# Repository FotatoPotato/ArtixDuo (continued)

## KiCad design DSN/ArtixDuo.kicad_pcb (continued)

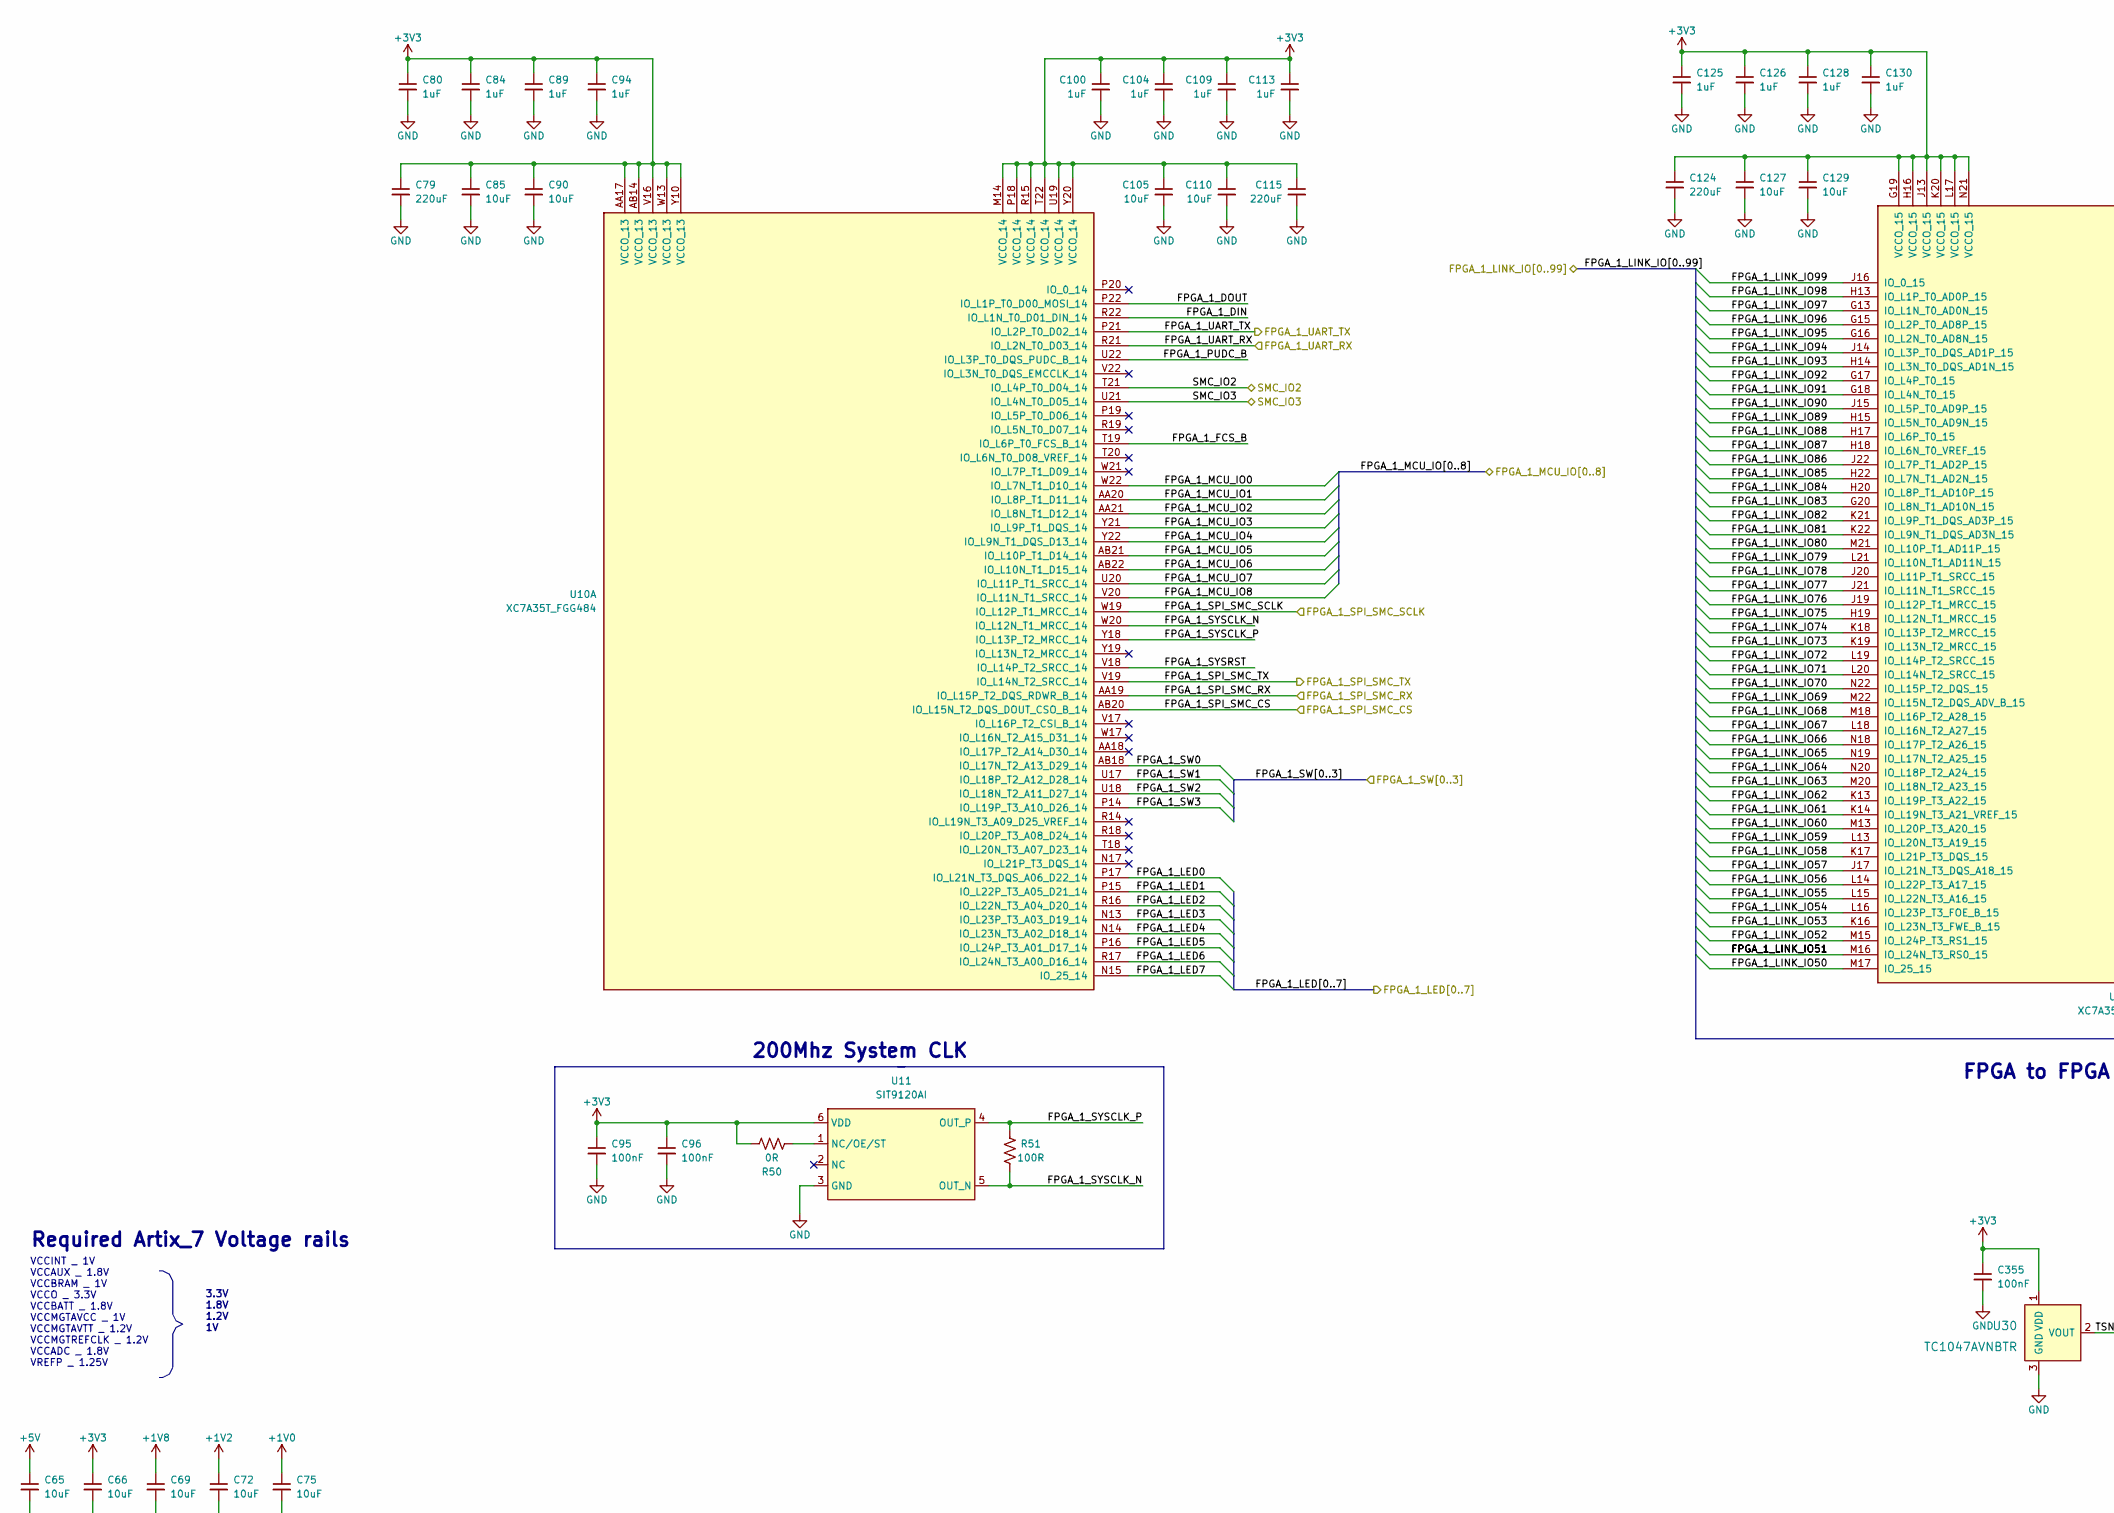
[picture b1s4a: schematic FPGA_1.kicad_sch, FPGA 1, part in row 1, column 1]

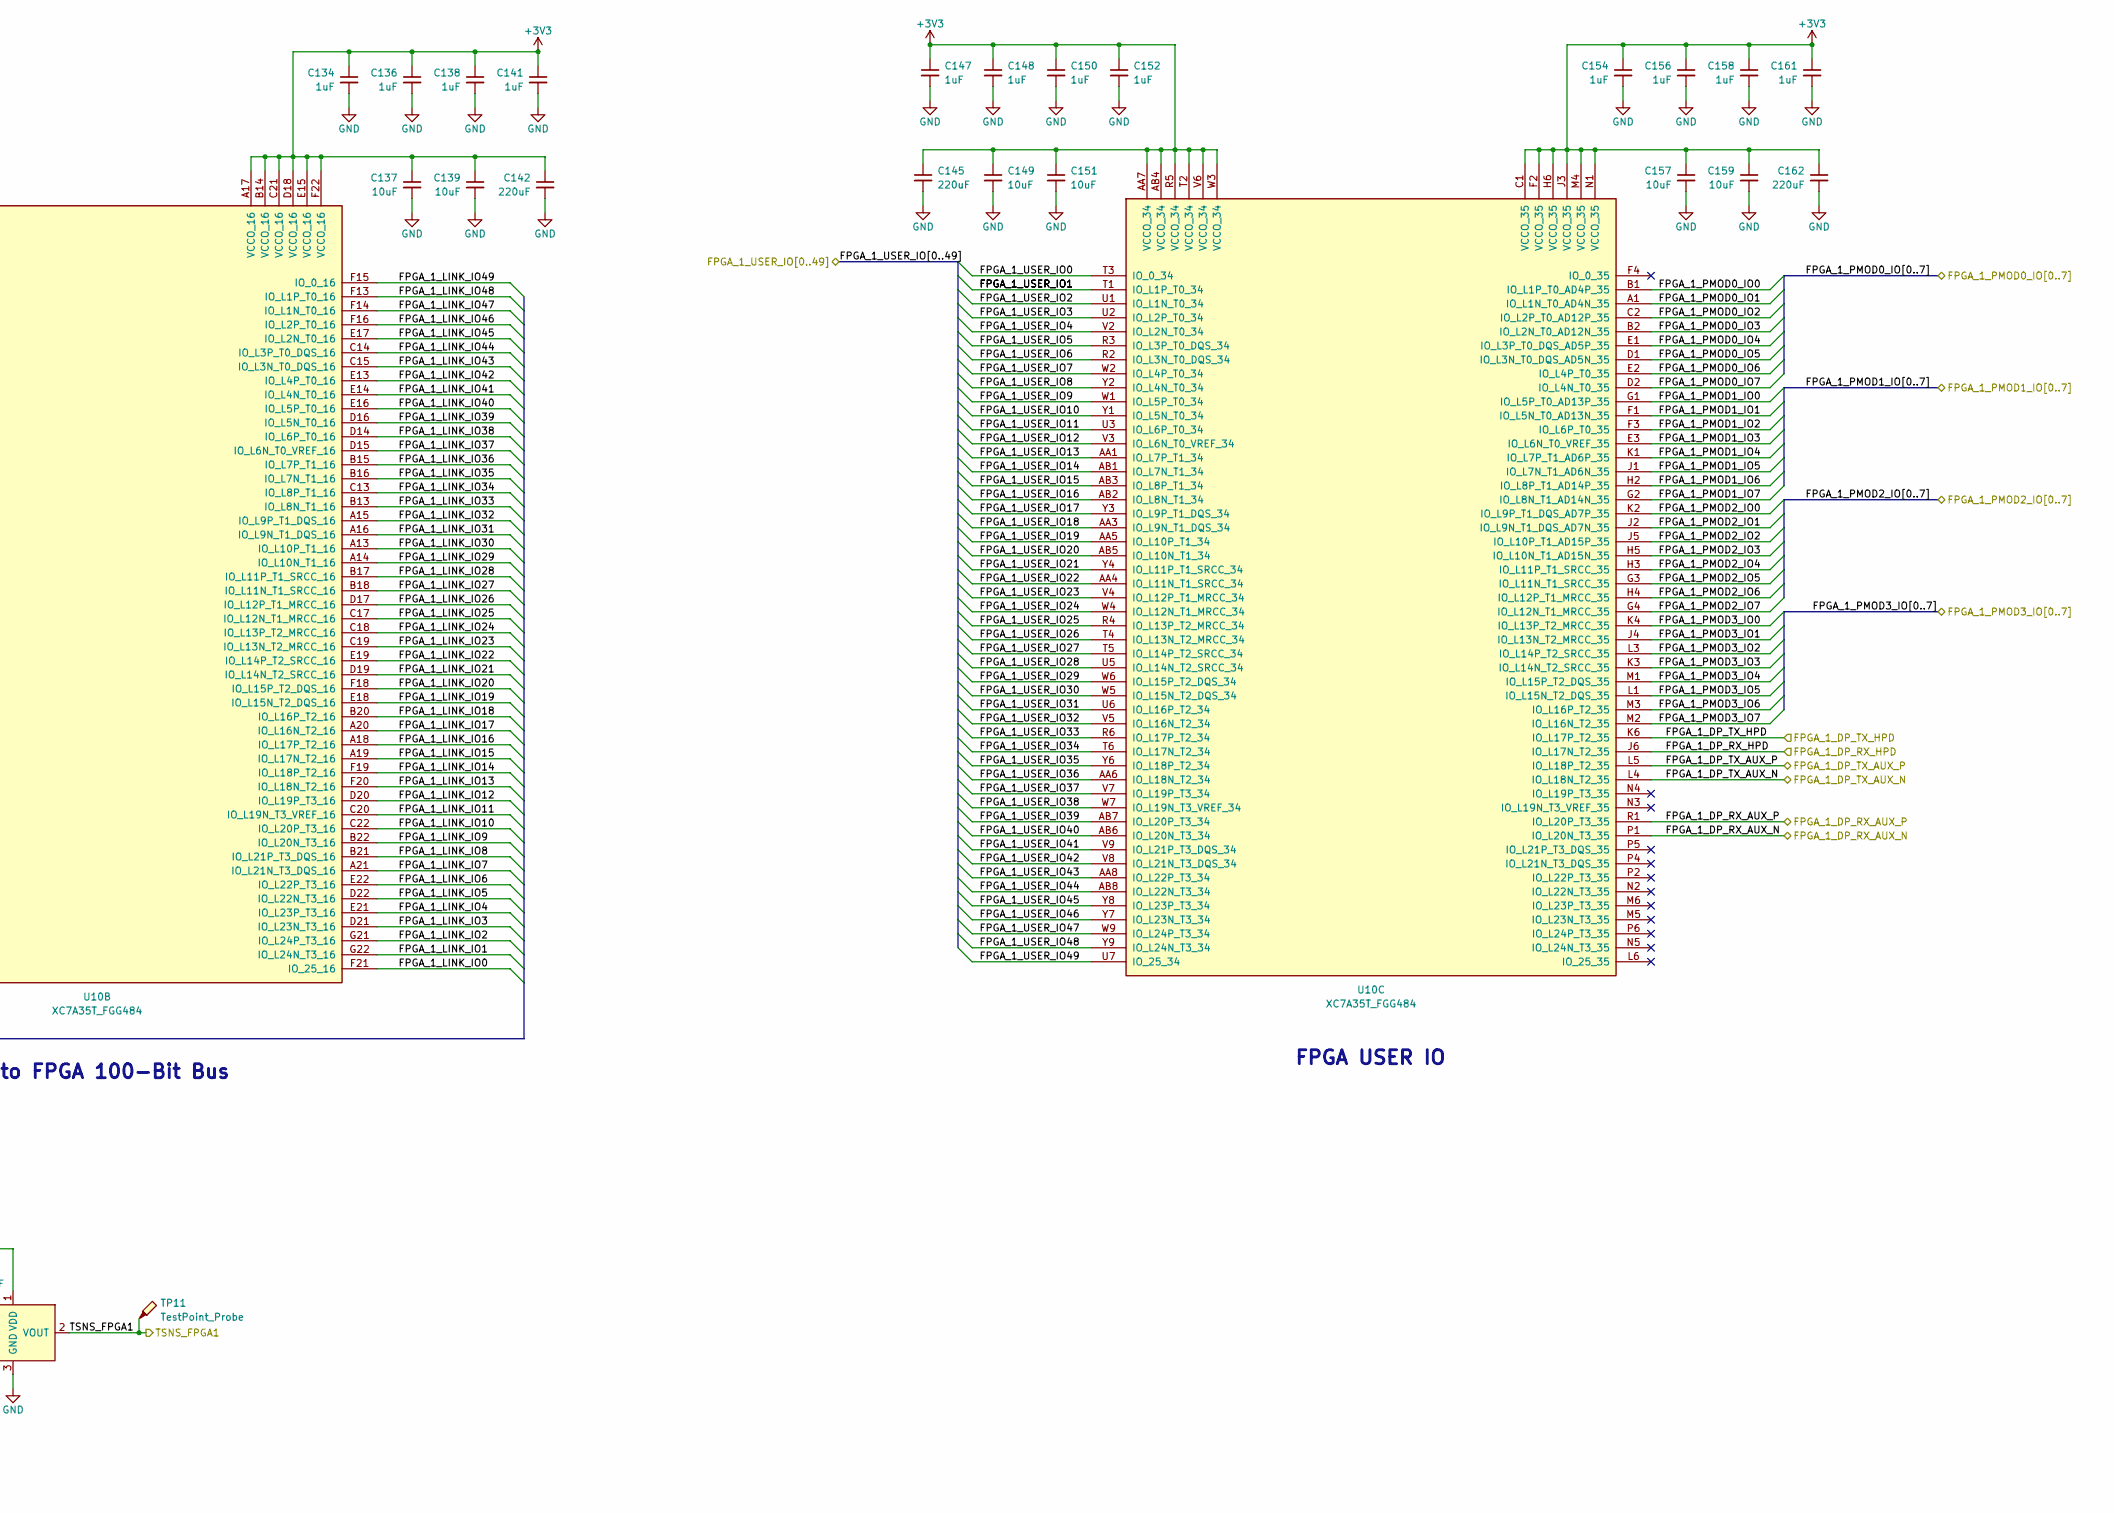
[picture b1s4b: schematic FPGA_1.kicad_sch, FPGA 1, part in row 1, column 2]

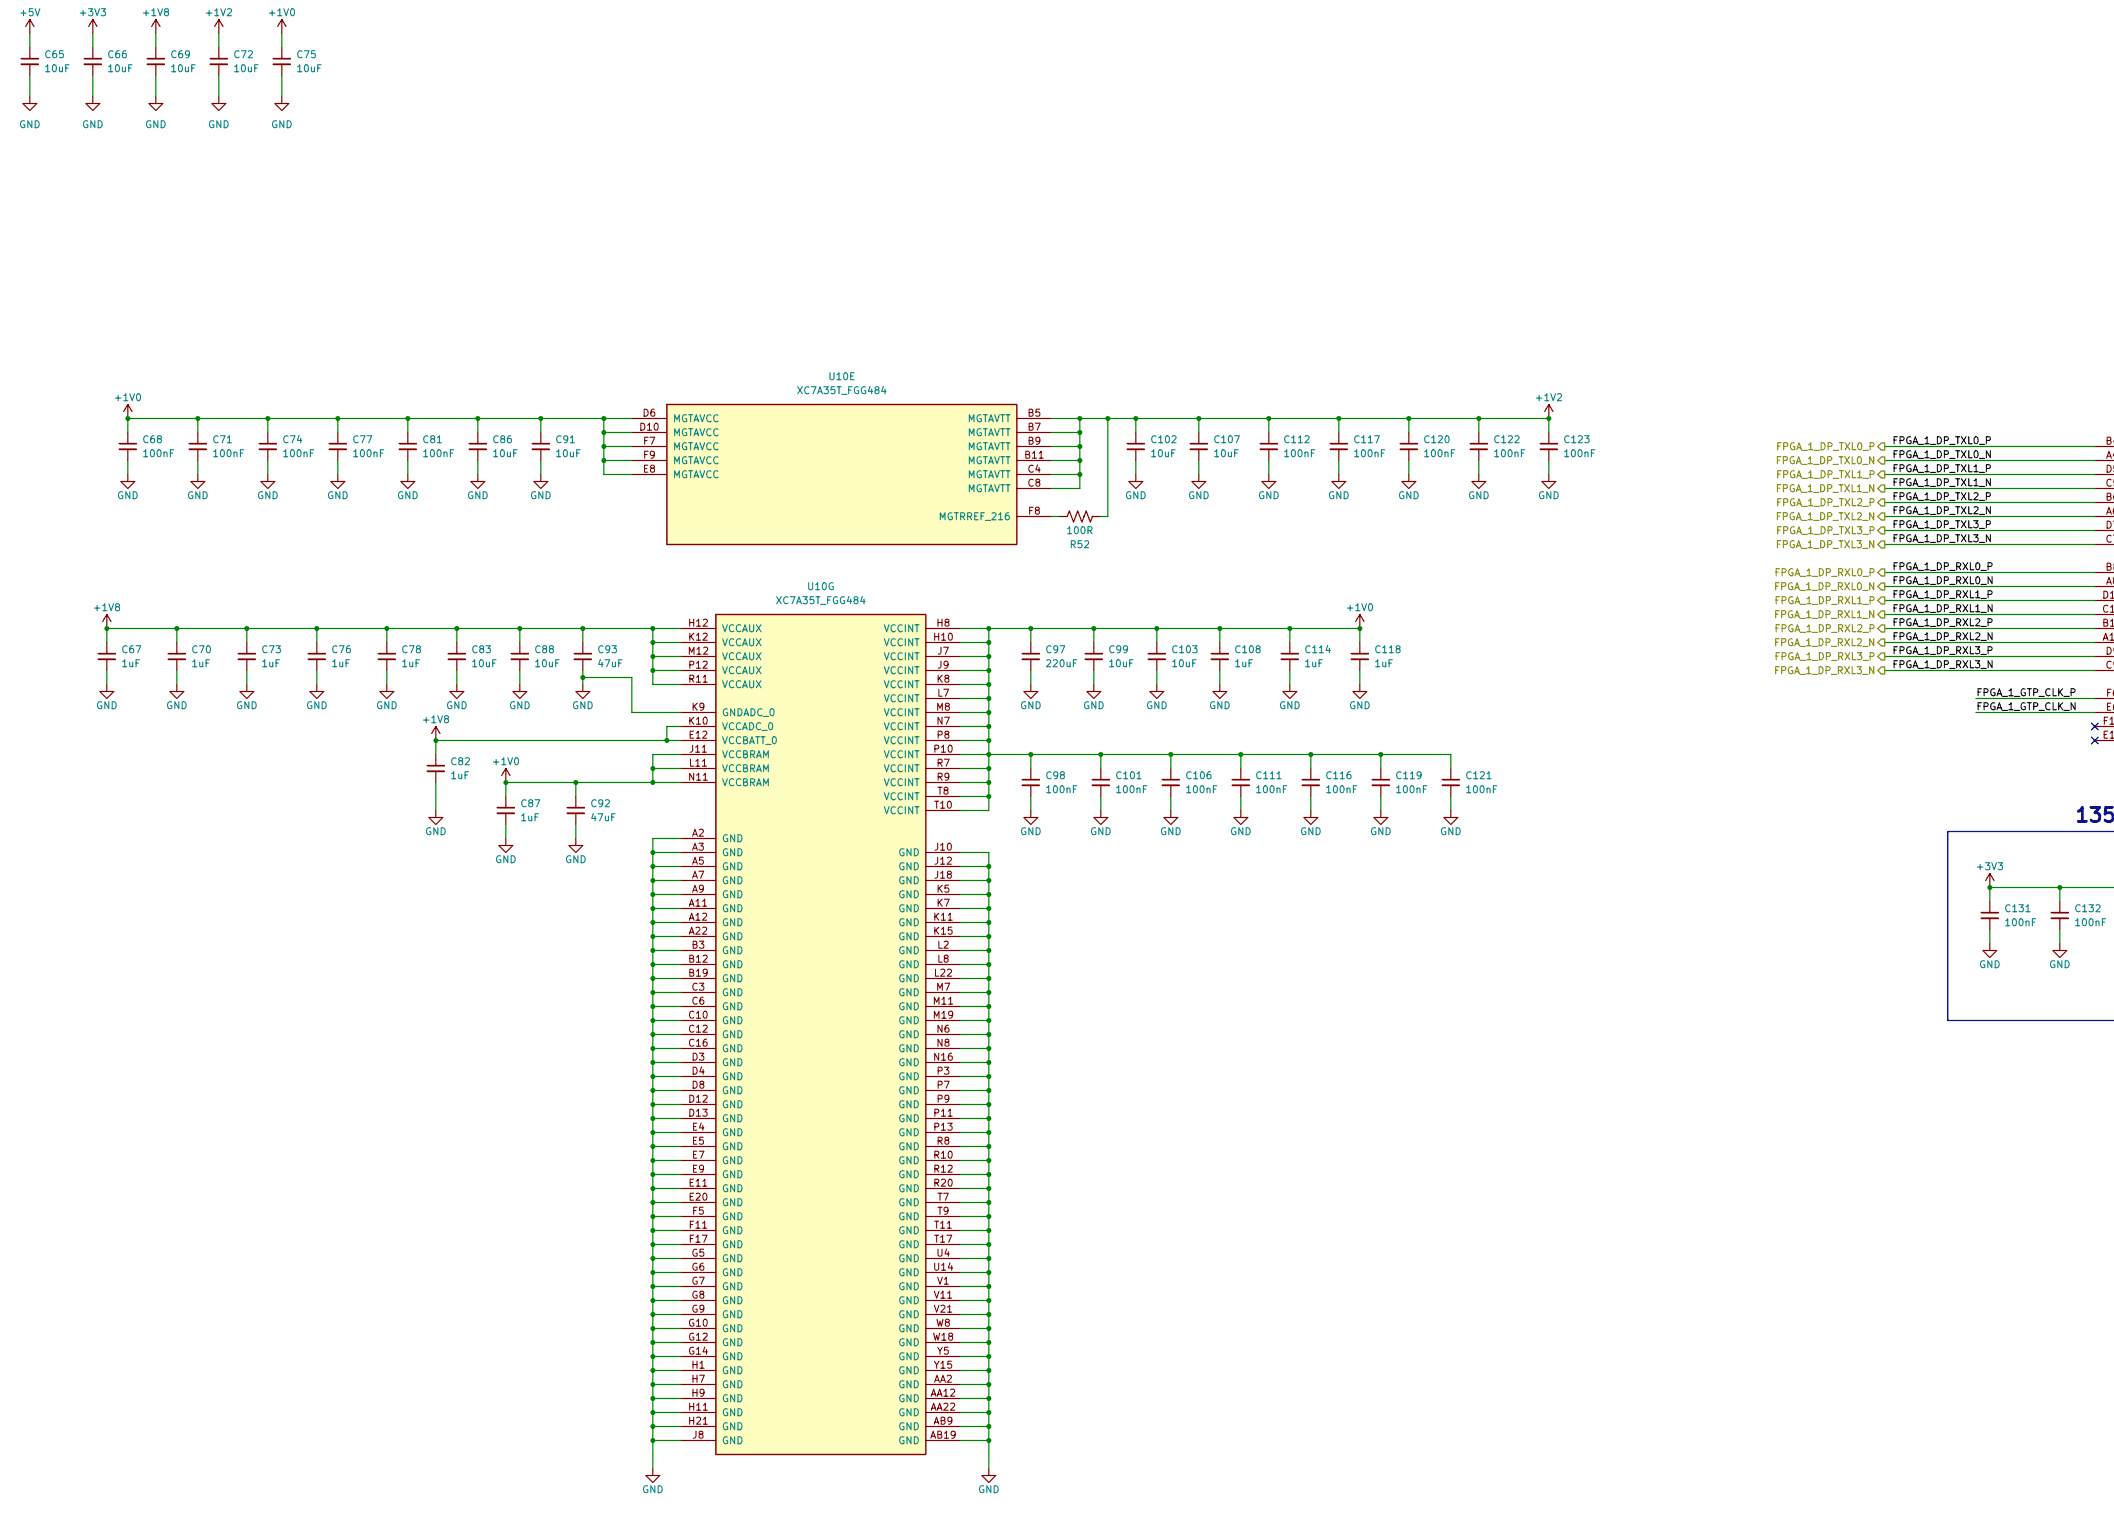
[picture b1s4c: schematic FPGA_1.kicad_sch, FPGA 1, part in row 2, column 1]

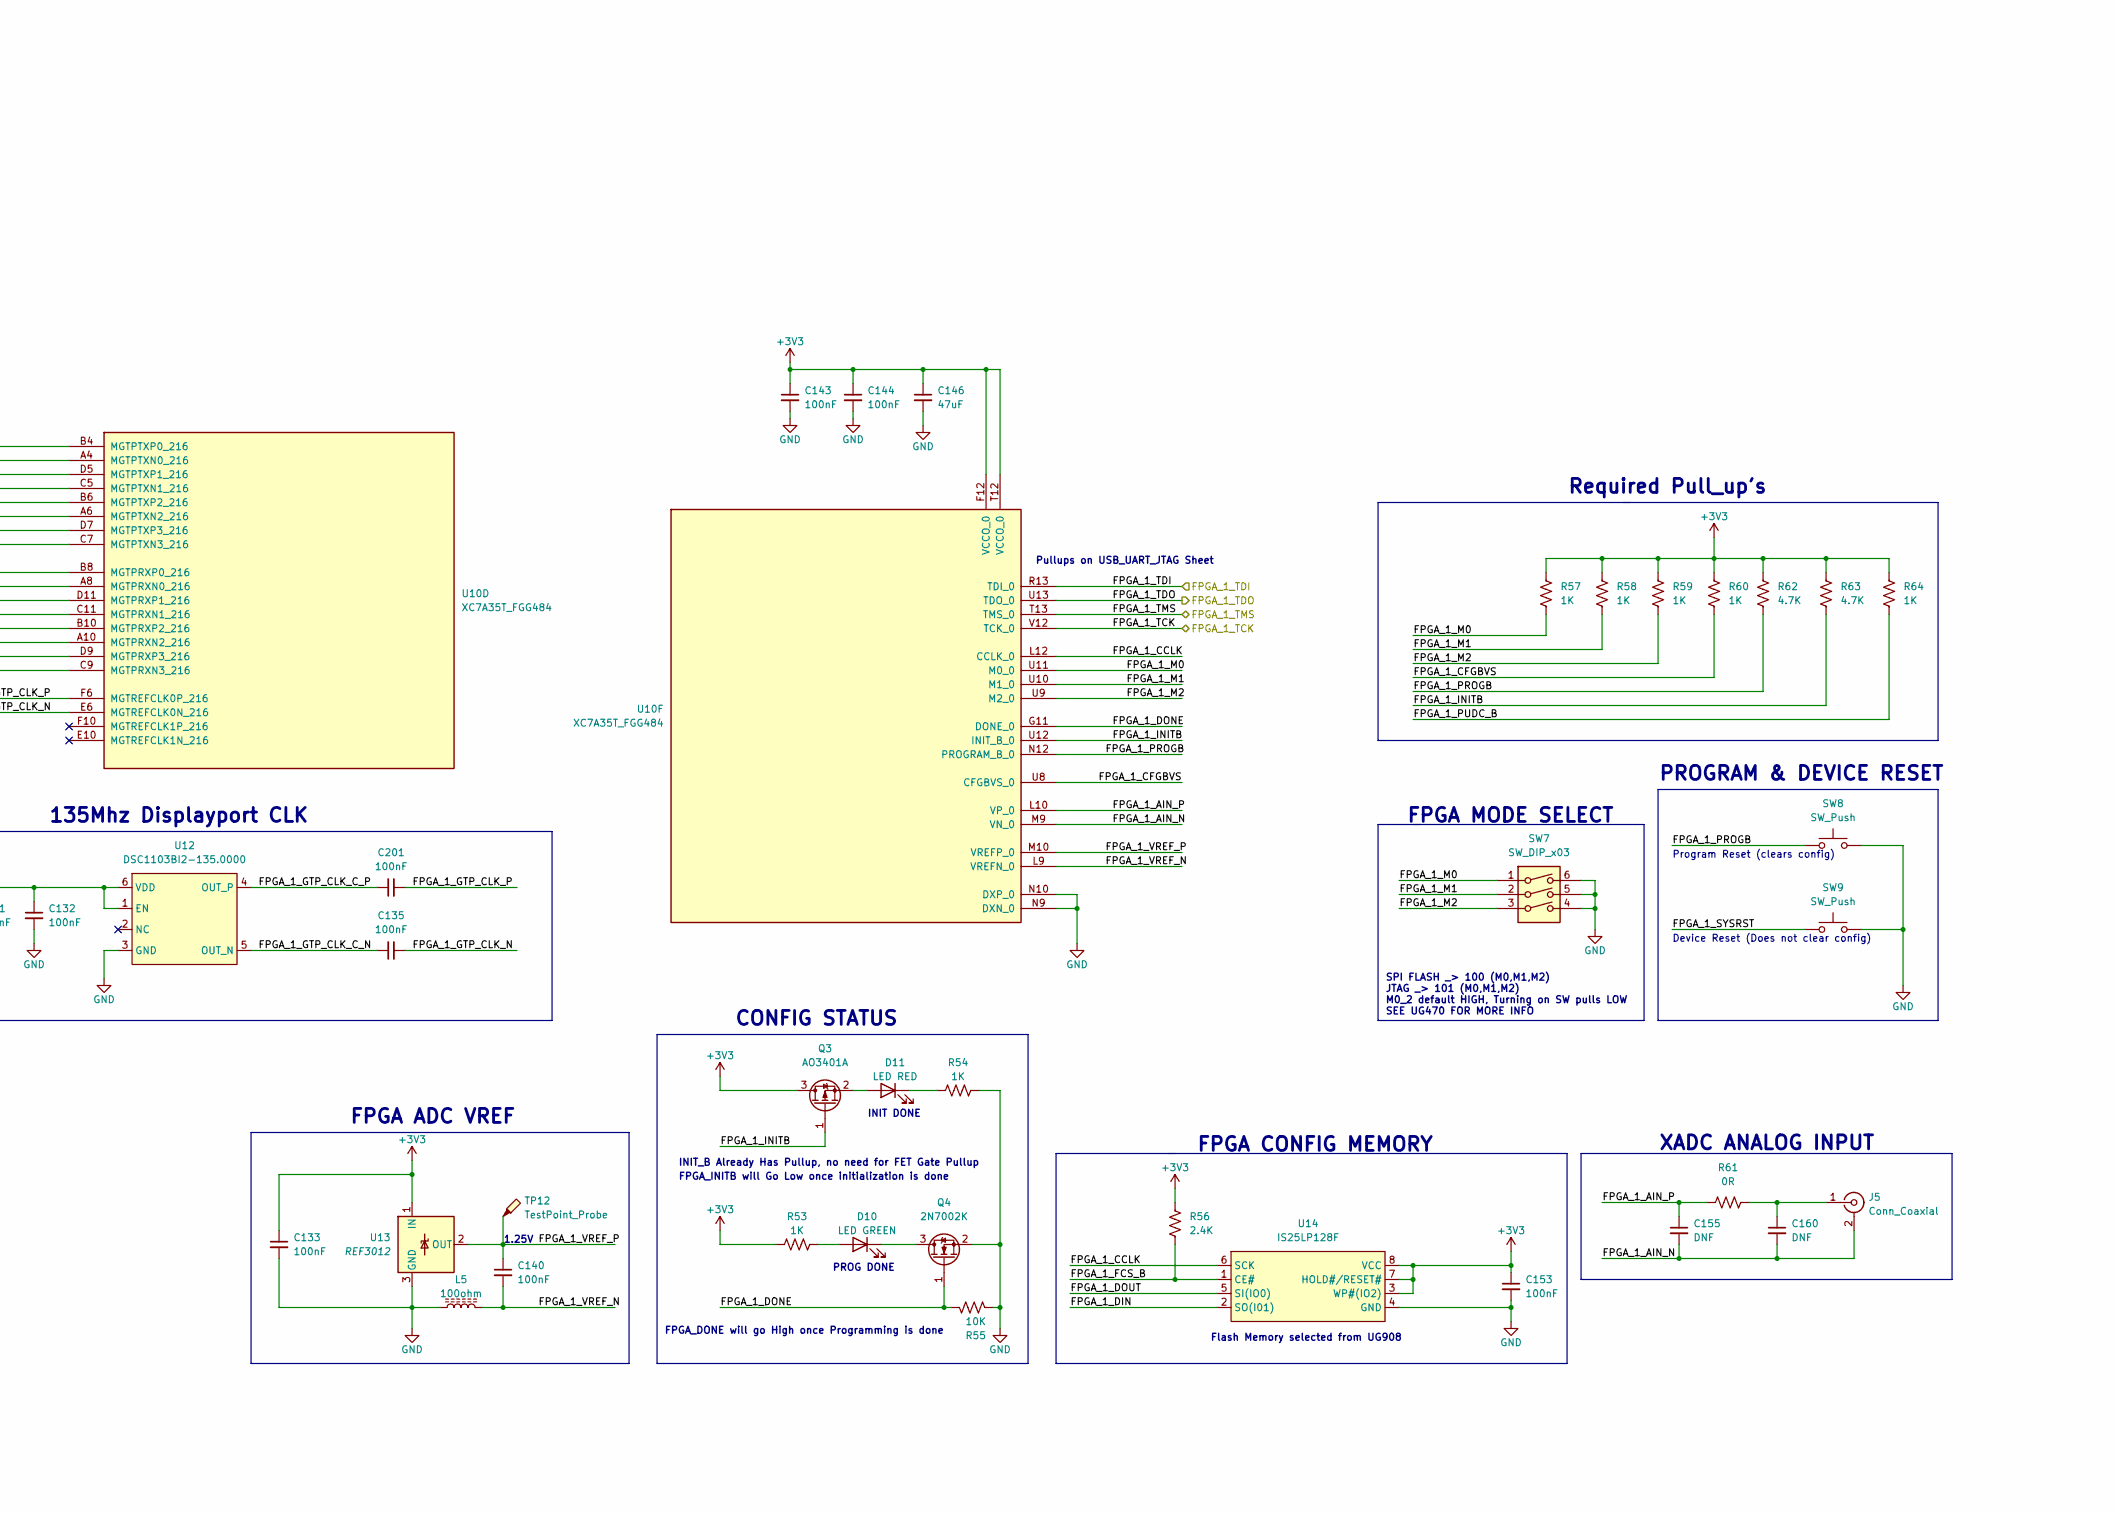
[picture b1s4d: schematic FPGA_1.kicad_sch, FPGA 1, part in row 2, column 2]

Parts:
C65, C66, C69, C72, C75: 10uF; C_0805_2012Metric; MFR PN GRM21BC71E106KE01K
C67, C70, C73, C76, C78, C80, C82, C84, C87, C89, C94, C100, C104, C108, C109, C113, C114, C118, C125, C126, C128, C130, C134, C136, C138, C141, C147, C148, C150, C152, C154, C156, C158, C161: 1uF; C_0402_1005Metric; MFR PN GRM153R61A105ME95D
C68, C71, C74, C77, C81, C95, C96, C98, C101, C106, C111, C112, C116, C117, C119, C120, C121, C122, C123, C131, C132, C135, C201: 100nF; C_0402_1005Metric; MFR PN GRM155R71E104KE14J
C79, C97, C115, C124, C142, C145, C162: 220uF; C_1210_3225Metric; MFR PN GRM32ER60J227ME05K
C83, C85, C86, C88, C90, C91, C99, C102, C103, C105, C107, C110, C127, C129, C137, C139, C149, C151, C157, C159: 10uF; C_0603_1608Metric; MFR PN GRM185R60J106ME15J
C92, C93: 47uF; C_1210_3225Metric; MFR PN GRM32ER70J476ME20L
C133, C140, C143, C144, C153, C355: 100nF; C_0402_1005Metric; MFR PN GRM155R71H104ME14J
C146: 47uF; C_1210_3225Metric
C155, C160: DNF; C_0402_1005Metric
D10: LED GREEN; LED_0603_1608Metric; MFR PN 150060VS75000
D11: LED RED; LED_0603_1608Metric; MFR PN 150060RS75000
J5: Conn_Coaxial; SMA_Amphenol_901-144_Vertical
L5: 100ohm; L_0402_1005Metric; MFR_PN 742792731
Q3: AO3401A; SOT-23
Q4: 2N7002K; SOT-23
R50, R61: 0R; R_0402_1005Metric
R51, R52: 100R; R_0402_1005Metric; MFR PN RC0402FR-07100RL
R53, R54, R57, R58, R59, R60, R64: 1K; R_0402_1005Metric
R55: 10K; R_0402_1005Metric; MFR PN RC0402FR-0710KP
R56: 2.4K; R_0402_1005Metric
R62, R63: 4.7K; R_0402_1005Metric
SW7: SW_DIP_x03; SW_DIP_SPSTx03_Slide_9.78x9.8mm_W8.61mm_P2.54mm
SW8, SW9: SW_Push; SW_Push_1P1T_NO_CK_KMR2
TP11, TP12: TestPoint_Probe; TestPoint_Loop_D2.50mm_Drill1.85mm
U10: XC7A35T_FGG484
U11: SIT9120AI; Oscillator_SMD_SiTime_SiT9121-6Pin_3.2x2.5mm
U12: DSC1103BI2-135.0000; VDFN-6
U13: REF3012; SOT-23
U14: IS25LP128F; SOIC-8_3.9x4.9mm_P1.27mm; MFR PN IS25LP128F-JBLA3
U30: TC1047AVNBTR; SOT-23-3; MPN TC1047AVNBTR; Digi-Key_PN TC1047AVNBCT-ND

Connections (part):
+1V0: C68.1, C71.1, C74.1, C75.1, C77.1, C81.1, C86.1, C87.1, C91.1, C92.1, C97.1, C98.1, C99.1, C101.1, C103.1, C106.1, C108.1, C111.1, C114.1, C116.1, C118.1, C119.1, C121.1, U10.D6 (MGTAVCC), U10.D10 (MGTAVCC), U10.E8 (MGTAVCC), U10.F7 (MGTAVCC), U10.F9 (MGTAVCC), U10.H8 (VCCINT), U10.H10 (VCCINT), U10.J7 (VCCINT), U10.J9 (VCCINT), U10.J11 (VCCBRAM), U10.K8 (VCCINT), U10.L7 (VCCINT), U10.L11 (VCCBRAM), U10.M8 (VCCINT), U10.N7 (VCCINT), U10.N11 (VCCBRAM), U10.P8 (VCCINT), U10.P10 (VCCINT), U10.R7 (VCCINT), U10.R9 (VCCINT), U10.T8 (VCCINT), U10.T10 (VCCINT); also elsewhere on the board
+1V2: C72.1, C102.1, C107.1, C112.1, C117.1, C120.1, C122.1, C123.1, R52.2, U10.B5 (MGTAVTT), U10.B7 (MGTAVTT), U10.B9 (MGTAVTT), U10.B11 (MGTAVTT), U10.C4 (MGTAVTT), U10.C8 (MGTAVTT); also elsewhere on the board
+1V8: C67.1, C69.1, C70.1, C73.1, C76.1, C78.1, C82.1, C83.1, C88.1, C93.1, U10.E12 (VCCBATT_0), U10.H12 (VCCAUX), U10.K10 (VCCADC_0), U10.K12 (VCCAUX), U10.M12 (VCCAUX), U10.P12 (VCCAUX), U10.R11 (VCCAUX); also elsewhere on the board
+3V3: C66.1, C79.1, C80.1, C84.1, C85.1, C89.1, C90.1, C94.1, C95.1, C96.1, C100.1, C104.1, C105.1, C109.1, C110.1, C113.1, C115.1, C124.1, C125.1, C126.1, C127.1, C128.1, C129.1, C130.1, C131.1, C132.1, C133.1, C134.1, C136.1, C137.1, C138.1, C139.1, C141.1, C142.1, C143.1, C144.1, C145.1, C146.1, C147.1, C148.1, C149.1, C150.1, C151.1, C152.1, C153.1, C154.1, C156.1, C157.1, C158.1, C159.1, C161.1, C162.1, C355.1, Q3.3 (D), R50.1, R53.2, R56.2, R57.2, R58.2, R59.2, R60.2, R62.2, R63.2, R64.2, U10.A17 (VCCO_16), U10.AA7 (VCCO_34), U10.AA17 (VCCO_13), U10.AB4 (VCCO_34), U10.AB14 (VCCO_13), U10.B14 (VCCO_16), U10.C1 (VCCO_35), U10.C21 (VCCO_16), U10.D18 (VCCO_16), U10.E15 (VCCO_16), U10.F2 (VCCO_35), U10.F12 (VCCO_0), U10.F22 (VCCO_16), U10.G19 (VCCO_15), U10.H6 (VCCO_35), U10.H16 (VCCO_15), U10.J3 (VCCO_35), U10.J13 (VCCO_15)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; also elsewhere on the board
/TopSheet/FPGA_0/FPGA_0_LINK_IO0: U10.F21 (IO_25_16); also elsewhere on the board
/TopSheet/FPGA_0/FPGA_0_LINK_IO1: U10.G22 (IO_L24N_T3_16); also elsewhere on the board
/TopSheet/FPGA_0/FPGA_0_LINK_IO2: U10.G21 (IO_L24P_T3_16); also elsewhere on the board
/TopSheet/FPGA_0/FPGA_0_LINK_IO3: U10.D21 (IO_L23N_T3_16); also elsewhere on the board
/TopSheet/FPGA_0/FPGA_0_LINK_IO4: U10.E21 (IO_L23P_T3_16); also elsewhere on the board
/TopSheet/FPGA_0/FPGA_0_LINK_IO5: U10.D22 (IO_L22N_T3_16); also elsewhere on the board
/TopSheet/FPGA_0/FPGA_0_LINK_IO6: U10.E22 (IO_L22P_T3_16); also elsewhere on the board
/TopSheet/FPGA_0/FPGA_0_LINK_IO7: U10.A21 (IO_L21N_T3_DQS_16); also elsewhere on the board
/TopSheet/FPGA_0/FPGA_0_LINK_IO8: U10.B21 (IO_L21P_T3_DQS_16); also elsewhere on the board
/TopSheet/FPGA_0/FPGA_0_LINK_IO9: U10.B22 (IO_L20N_T3_16); also elsewhere on the board
/TopSheet/FPGA_0/FPGA_0_LINK_IO10: U10.C22 (IO_L20P_T3_16); also elsewhere on the board
/TopSheet/FPGA_0/FPGA_0_LINK_IO11: U10.C20 (IO_L19N_T3_VREF_16); also elsewhere on the board
/TopSheet/FPGA_0/FPGA_0_LINK_IO12: U10.D20 (IO_L19P_T3_16); also elsewhere on the board
/TopSheet/FPGA_0/FPGA_0_LINK_IO13: U10.F20 (IO_L18N_T2_16); also elsewhere on the board
/TopSheet/FPGA_0/FPGA_0_LINK_IO14: U10.F19 (IO_L18P_T2_16); also elsewhere on the board
/TopSheet/FPGA_0/FPGA_0_LINK_IO15: U10.A19 (IO_L17N_T2_16); also elsewhere on the board
/TopSheet/FPGA_0/FPGA_0_LINK_IO16: U10.A18 (IO_L17P_T2_16); also elsewhere on the board
/TopSheet/FPGA_0/FPGA_0_LINK_IO17: U10.A20 (IO_L16N_T2_16); also elsewhere on the board
/TopSheet/FPGA_0/FPGA_0_LINK_IO18: U10.B20 (IO_L16P_T2_16); also elsewhere on the board
/TopSheet/FPGA_0/FPGA_0_LINK_IO19: U10.E18 (IO_L15N_T2_DQS_16); also elsewhere on the board
/TopSheet/FPGA_0/FPGA_0_LINK_IO20: U10.F18 (IO_L15P_T2_DQS_16); also elsewhere on the board
/TopSheet/FPGA_0/FPGA_0_LINK_IO21: U10.D19 (IO_L14N_T2_SRCC_16); also elsewhere on the board
/TopSheet/FPGA_0/FPGA_0_LINK_IO22: U10.E19 (IO_L14P_T2_SRCC_16); also elsewhere on the board
/TopSheet/FPGA_0/FPGA_0_LINK_IO23: U10.C19 (IO_L13N_T2_MRCC_16); also elsewhere on the board
/TopSheet/FPGA_0/FPGA_0_LINK_IO24: U10.C18 (IO_L13P_T2_MRCC_16); also elsewhere on the board
/TopSheet/FPGA_0/FPGA_0_LINK_IO25: U10.C17 (IO_L12N_T1_MRCC_16); also elsewhere on the board
/TopSheet/FPGA_0/FPGA_0_LINK_IO26: U10.D17 (IO_L12P_T1_MRCC_16); also elsewhere on the board
/TopSheet/FPGA_0/FPGA_0_LINK_IO27: U10.B18 (IO_L11N_T1_SRCC_16); also elsewhere on the board
/TopSheet/FPGA_0/FPGA_0_LINK_IO28: U10.B17 (IO_L11P_T1_SRCC_16); also elsewhere on the board
/TopSheet/FPGA_0/FPGA_0_LINK_IO29: U10.A14 (IO_L10N_T1_16); also elsewhere on the board
/TopSheet/FPGA_0/FPGA_0_LINK_IO30: U10.A13 (IO_L10P_T1_16); also elsewhere on the board
/TopSheet/FPGA_0/FPGA_0_LINK_IO31: U10.A16 (IO_L9N_T1_DQS_16); also elsewhere on the board
/TopSheet/FPGA_0/FPGA_0_LINK_IO32: U10.A15 (IO_L9P_T1_DQS_16); also elsewhere on the board
/TopSheet/FPGA_0/FPGA_0_LINK_IO33: U10.B13 (IO_L8N_T1_16); also elsewhere on the board
/TopSheet/FPGA_0/FPGA_0_LINK_IO34: U10.C13 (IO_L8P_T1_16); also elsewhere on the board
/TopSheet/FPGA_0/FPGA_0_LINK_IO35: U10.B16 (IO_L7N_T1_16); also elsewhere on the board
/TopSheet/FPGA_0/FPGA_0_LINK_IO36: U10.B15 (IO_L7P_T1_16); also elsewhere on the board
/TopSheet/FPGA_0/FPGA_0_LINK_IO37: U10.D15 (IO_L6N_T0_VREF_16); also elsewhere on the board
/TopSheet/FPGA_0/FPGA_0_LINK_IO38: U10.D14 (IO_L6P_T0_16); also elsewhere on the board
/TopSheet/FPGA_0/FPGA_0_LINK_IO39: U10.D16 (IO_L5N_T0_16); also elsewhere on the board
/TopSheet/FPGA_0/FPGA_0_LINK_IO40: U10.E16 (IO_L5P_T0_16); also elsewhere on the board
/TopSheet/FPGA_0/FPGA_0_LINK_IO41: U10.E14 (IO_L4N_T0_16); also elsewhere on the board
/TopSheet/FPGA_0/FPGA_0_LINK_IO42: U10.E13 (IO_L4P_T0_16); also elsewhere on the board
/TopSheet/FPGA_0/FPGA_0_LINK_IO43: U10.C15 (IO_L3N_T0_DQS_16); also elsewhere on the board
/TopSheet/FPGA_0/FPGA_0_LINK_IO44: U10.C14 (IO_L3P_T0_DQS_16); also elsewhere on the board
/TopSheet/FPGA_0/FPGA_0_LINK_IO45: U10.E17 (IO_L2N_T0_16); also elsewhere on the board
/TopSheet/FPGA_0/FPGA_0_LINK_IO46: U10.F16 (IO_L2P_T0_16); also elsewhere on the board
/TopSheet/FPGA_0/FPGA_0_LINK_IO47: U10.F14 (IO_L1N_T0_16); also elsewhere on the board
/TopSheet/FPGA_0/FPGA_0_LINK_IO48: U10.F13 (IO_L1P_T0_16); also elsewhere on the board
/TopSheet/FPGA_0/FPGA_0_LINK_IO49: U10.F15 (IO_0_16); also elsewhere on the board
/TopSheet/FPGA_0/FPGA_0_LINK_IO50: U10.M17 (IO_25_15); also elsewhere on the board
/TopSheet/FPGA_0/FPGA_0_LINK_IO52: U10.M15 (IO_L24P_T3_RS1_15); also elsewhere on the board
/TopSheet/FPGA_0/FPGA_0_LINK_IO53: U10.K16 (IO_L23N_T3_FWE_B_15); also elsewhere on the board
/TopSheet/FPGA_0/FPGA_0_LINK_IO54: U10.L16 (IO_L23P_T3_FOE_B_15); also elsewhere on the board
/TopSheet/FPGA_0/FPGA_0_LINK_IO55: U10.L15 (IO_L22N_T3_A16_15); also elsewhere on the board
/TopSheet/FPGA_0/FPGA_0_LINK_IO56: U10.L14 (IO_L22P_T3_A17_15); also elsewhere on the board
/TopSheet/FPGA_0/FPGA_0_LINK_IO57: U10.J17 (IO_L21N_T3_DQS_A18_15); also elsewhere on the board
/TopSheet/FPGA_0/FPGA_0_LINK_IO58: U10.K17 (IO_L21P_T3_DQS_15); also elsewhere on the board
/TopSheet/FPGA_0/FPGA_0_LINK_IO59: U10.L13 (IO_L20N_T3_A19_15); also elsewhere on the board
/TopSheet/FPGA_0/FPGA_0_LINK_IO60: U10.M13 (IO_L20P_T3_A20_15); also elsewhere on the board
/TopSheet/FPGA_0/FPGA_0_LINK_IO61: U10.K14 (IO_L19N_T3_A21_VREF_15); also elsewhere on the board
/TopSheet/FPGA_0/FPGA_0_LINK_IO62: U10.K13 (IO_L19P_T3_A22_15); also elsewhere on the board
/TopSheet/FPGA_0/FPGA_0_LINK_IO63: U10.M20 (IO_L18N_T2_A23_15); also elsewhere on the board
/TopSheet/FPGA_0/FPGA_0_LINK_IO64: U10.N20 (IO_L18P_T2_A24_15); also elsewhere on the board
/TopSheet/FPGA_0/FPGA_0_LINK_IO65: U10.N19 (IO_L17N_T2_A25_15); also elsewhere on the board
/TopSheet/FPGA_0/FPGA_0_LINK_IO66: U10.N18 (IO_L17P_T2_A26_15); also elsewhere on the board
/TopSheet/FPGA_0/FPGA_0_LINK_IO67: U10.L18 (IO_L16N_T2_A27_15); also elsewhere on the board
/TopSheet/FPGA_0/FPGA_0_LINK_IO68: U10.M18 (IO_L16P_T2_A28_15); also elsewhere on the board
/TopSheet/FPGA_0/FPGA_0_LINK_IO69: U10.M22 (IO_L15N_T2_DQS_ADV_B_15); also elsewhere on the board
/TopSheet/FPGA_0/FPGA_0_LINK_IO70: U10.N22 (IO_L15P_T2_DQS_15); also elsewhere on the board
/TopSheet/FPGA_0/FPGA_0_LINK_IO71: U10.L20 (IO_L14N_T2_SRCC_15); also elsewhere on the board
/TopSheet/FPGA_0/FPGA_0_LINK_IO72: U10.L19 (IO_L14P_T2_SRCC_15); also elsewhere on the board
/TopSheet/FPGA_0/FPGA_0_LINK_IO73: U10.K19 (IO_L13N_T2_MRCC_15); also elsewhere on the board
/TopSheet/FPGA_0/FPGA_0_LINK_IO74: U10.K18 (IO_L13P_T2_MRCC_15); also elsewhere on the board
/TopSheet/FPGA_0/FPGA_0_LINK_IO75: U10.H19 (IO_L12N_T1_MRCC_15); also elsewhere on the board
/TopSheet/FPGA_0/FPGA_0_LINK_IO76: U10.J19 (IO_L12P_T1_MRCC_15); also elsewhere on the board
/TopSheet/FPGA_0/FPGA_0_LINK_IO77: U10.J21 (IO_L11N_T1_SRCC_15); also elsewhere on the board
/TopSheet/FPGA_0/FPGA_0_LINK_IO78: U10.J20 (IO_L11P_T1_SRCC_15); also elsewhere on the board
/TopSheet/FPGA_0/FPGA_0_LINK_IO79: U10.L21 (IO_L10N_T1_AD11N_15); also elsewhere on the board
/TopSheet/FPGA_0/FPGA_0_LINK_IO80: U10.M21 (IO_L10P_T1_AD11P_15); also elsewhere on the board
/TopSheet/FPGA_0/FPGA_0_LINK_IO81: U10.K22 (IO_L9N_T1_DQS_AD3N_15); also elsewhere on the board
/TopSheet/FPGA_0/FPGA_0_LINK_IO82: U10.K21 (IO_L9P_T1_DQS_AD3P_15); also elsewhere on the board
/TopSheet/FPGA_0/FPGA_0_LINK_IO83: U10.G20 (IO_L8N_T1_AD10N_15); also elsewhere on the board
/TopSheet/FPGA_0/FPGA_0_LINK_IO84: U10.H20 (IO_L8P_T1_AD10P_15); also elsewhere on the board
/TopSheet/FPGA_0/FPGA_0_LINK_IO85: U10.H22 (IO_L7N_T1_AD2N_15); also elsewhere on the board
/TopSheet/FPGA_0/FPGA_0_LINK_IO86: U10.J22 (IO_L7P_T1_AD2P_15); also elsewhere on the board
/TopSheet/FPGA_0/FPGA_0_LINK_IO87: U10.H18 (IO_L6N_T0_VREF_15); also elsewhere on the board
/TopSheet/FPGA_0/FPGA_0_LINK_IO88: U10.H17 (IO_L6P_T0_15); also elsewhere on the board
/TopSheet/FPGA_0/FPGA_0_LINK_IO89: U10.H15 (IO_L5N_T0_AD9N_15); also elsewhere on the board
/TopSheet/FPGA_0/FPGA_0_LINK_IO90: U10.J15 (IO_L5P_T0_AD9P_15); also elsewhere on the board
/TopSheet/FPGA_0/FPGA_0_LINK_IO91: U10.G18 (IO_L4N_T0_15); also elsewhere on the board
/TopSheet/FPGA_0/FPGA_0_LINK_IO92: U10.G17 (IO_L4P_T0_15); also elsewhere on the board
/TopSheet/FPGA_0/FPGA_0_LINK_IO93: U10.H14 (IO_L3N_T0_DQS_AD1N_15); also elsewhere on the board
/TopSheet/FPGA_0/FPGA_0_LINK_IO94: U10.J14 (IO_L3P_T0_DQS_AD1P_15); also elsewhere on the board
/TopSheet/FPGA_0/FPGA_0_LINK_IO95: U10.G16 (IO_L2N_T0_AD8N_15); also elsewhere on the board
/TopSheet/FPGA_0/FPGA_0_LINK_IO96: U10.G15 (IO_L2P_T0_AD8P_15); also elsewhere on the board
/TopSheet/FPGA_0/FPGA_0_LINK_IO97: U10.G13 (IO_L1N_T0_AD0N_15); also elsewhere on the board
/TopSheet/FPGA_0/FPGA_0_LINK_IO98: U10.H13 (IO_L1P_T0_AD0P_15); also elsewhere on the board
/TopSheet/FPGA_0/FPGA_0_LINK_IO99: U10.J16 (IO_0_15); also elsewhere on the board
/TopSheet/FPGA_1/FPGA_1_AIN_N: C155.2, C160.2, J5.2 (Ext), U10.M9 (VN_0)
/TopSheet/FPGA_1/FPGA_1_AIN_P: C155.1, R61.1, U10.L10 (VP_0)
/TopSheet/FPGA_1/FPGA_1_CCLK: U10.L12 (CCLK_0), U14.6 (SCK)
/TopSheet/FPGA_1/FPGA_1_CFGBVS: R60.1, U10.U8 (CFGBVS_0)
/TopSheet/FPGA_1/FPGA_1_DIN: U10.R22 (IO_L1N_T0_D01_DIN_14), U14.2 (SO(I01))
/TopSheet/FPGA_1/FPGA_1_DONE: Q4.1 (G), R55.1, U10.G11 (DONE_0)
/TopSheet/FPGA_1/FPGA_1_DOUT: U10.P22 (IO_L1P_T0_D00_MOSI_14), U14.5 (SI(IO0))
/TopSheet/FPGA_1/FPGA_1_DP_RXL0_N: U10.A8 (MGTPRXN0_216); also elsewhere on the board
/TopSheet/FPGA_1/FPGA_1_DP_RXL0_P: U10.B8 (MGTPRXP0_216); also elsewhere on the board
/TopSheet/FPGA_1/FPGA_1_DP_RXL1_N: U10.C11 (MGTPRXN1_216); also elsewhere on the board
/TopSheet/FPGA_1/FPGA_1_DP_RXL1_P: U10.D11 (MGTPRXP1_216); also elsewhere on the board
/TopSheet/FPGA_1/FPGA_1_DP_RXL2_N: U10.A10 (MGTPRXN2_216); also elsewhere on the board
/TopSheet/FPGA_1/FPGA_1_DP_RXL2_P: U10.B10 (MGTPRXP2_216); also elsewhere on the board
/TopSheet/FPGA_1/FPGA_1_DP_RXL3_N: U10.C9 (MGTPRXN3_216); also elsewhere on the board
/TopSheet/FPGA_1/FPGA_1_DP_RXL3_P: U10.D9 (MGTPRXP3_216); also elsewhere on the board
/TopSheet/FPGA_1/FPGA_1_DP_RX_AUX_N: U10.P1 (IO_L20N_T3_35); also elsewhere on the board
/TopSheet/FPGA_1/FPGA_1_DP_RX_AUX_P: U10.R1 (IO_L20P_T3_35); also elsewhere on the board
/TopSheet/FPGA_1/FPGA_1_DP_RX_HPD: U10.J6 (IO_L17N_T2_35); also elsewhere on the board
/TopSheet/FPGA_1/FPGA_1_DP_TXL0_N: U10.A4 (MGTPTXN0_216); also elsewhere on the board
/TopSheet/FPGA_1/FPGA_1_DP_TXL0_P: U10.B4 (MGTPTXP0_216); also elsewhere on the board
/TopSheet/FPGA_1/FPGA_1_DP_TXL1_N: U10.C5 (MGTPTXN1_216); also elsewhere on the board
/TopSheet/FPGA_1/FPGA_1_DP_TXL1_P: U10.D5 (MGTPTXP1_216); also elsewhere on the board
/TopSheet/FPGA_1/FPGA_1_DP_TXL2_N: U10.A6 (MGTPTXN2_216); also elsewhere on the board
/TopSheet/FPGA_1/FPGA_1_DP_TXL2_P: U10.B6 (MGTPTXP2_216); also elsewhere on the board
/TopSheet/FPGA_1/FPGA_1_DP_TXL3_N: U10.C7 (MGTPTXN3_216); also elsewhere on the board
/TopSheet/FPGA_1/FPGA_1_DP_TXL3_P: U10.D7 (MGTPTXP3_216); also elsewhere on the board
/TopSheet/FPGA_1/FPGA_1_DP_TX_AUX_N: U10.L4 (IO_L18N_T2_35); also elsewhere on the board
/TopSheet/FPGA_1/FPGA_1_DP_TX_AUX_P: U10.L5 (IO_L18P_T2_35); also elsewhere on the board
/TopSheet/FPGA_1/FPGA_1_DP_TX_HPD: U10.K6 (IO_L17P_T2_35); also elsewhere on the board
/TopSheet/FPGA_1/FPGA_1_FCS_B: R56.1, U10.T19 (IO_L6P_T0_FCS_B_14), U14.1 (CE#)
/TopSheet/FPGA_1/FPGA_1_GTP_CLK_C_N: C135.1, U12.5 (OUT_N)
/TopSheet/FPGA_1/FPGA_1_GTP_CLK_C_P: C201.1, U12.4 (OUT_P)
/TopSheet/FPGA_1/FPGA_1_GTP_CLK_N: C135.2, U10.E6 (MGTREFCLK0N_216)
/TopSheet/FPGA_1/FPGA_1_GTP_CLK_P: C201.2, U10.F6 (MGTREFCLK0P_216)
/TopSheet/FPGA_1/FPGA_1_INITB: Q3.1 (G), R63.1, U10.U12 (INIT_B_0)
/TopSheet/FPGA_1/FPGA_1_LED0: U10.P17 (IO_L21N_T3_DQS_A06_D22_14); also elsewhere on the board
/TopSheet/FPGA_1/FPGA_1_LED1: U10.P15 (IO_L22P_T3_A05_D21_14); also elsewhere on the board
/TopSheet/FPGA_1/FPGA_1_LED2: U10.R16 (IO_L22N_T3_A04_D20_14); also elsewhere on the board
/TopSheet/FPGA_1/FPGA_1_LED3: U10.N13 (IO_L23P_T3_A03_D19_14); also elsewhere on the board
/TopSheet/FPGA_1/FPGA_1_LED4: U10.N14 (IO_L23N_T3_A02_D18_14); also elsewhere on the board
/TopSheet/FPGA_1/FPGA_1_LED5: U10.P16 (IO_L24P_T3_A01_D17_14); also elsewhere on the board
/TopSheet/FPGA_1/FPGA_1_LED6: U10.R17 (IO_L24N_T3_A00_D16_14); also elsewhere on the board
/TopSheet/FPGA_1/FPGA_1_LED7: U10.N15 (IO_25_14); also elsewhere on the board
/TopSheet/FPGA_1/FPGA_1_M0: R57.1, SW7.1, U10.U11 (M0_0)
/TopSheet/FPGA_1/FPGA_1_M1: R58.1, SW7.2, U10.U10 (M1_0)
/TopSheet/FPGA_1/FPGA_1_M2: R59.1, SW7.3, U10.U9 (M2_0)
/TopSheet/FPGA_1/FPGA_1_MCU_IO0: U10.W22 (IO_L7N_T1_D10_14); also elsewhere on the board
/TopSheet/FPGA_1/FPGA_1_MCU_IO1: U10.AA20 (IO_L8P_T1_D11_14); also elsewhere on the board
/TopSheet/FPGA_1/FPGA_1_MCU_IO2: U10.AA21 (IO_L8N_T1_D12_14); also elsewhere on the board
/TopSheet/FPGA_1/FPGA_1_MCU_IO3: U10.Y21 (IO_L9P_T1_DQS_14); also elsewhere on the board
/TopSheet/FPGA_1/FPGA_1_MCU_IO4: U10.Y22 (IO_L9N_T1_DQS_D13_14); also elsewhere on the board
/TopSheet/FPGA_1/FPGA_1_MCU_IO5: U10.AB21 (IO_L10P_T1_D14_14); also elsewhere on the board
/TopSheet/FPGA_1/FPGA_1_MCU_IO6: U10.AB22 (IO_L10N_T1_D15_14); also elsewhere on the board
/TopSheet/FPGA_1/FPGA_1_MCU_IO7: U10.U20 (IO_L11P_T1_SRCC_14); also elsewhere on the board
/TopSheet/FPGA_1/FPGA_1_MCU_IO8: U10.V20 (IO_L11N_T1_SRCC_14); also elsewhere on the board
/TopSheet/FPGA_1/FPGA_1_PMOD0_IO0: U10.B1 (IO_L1P_T0_AD4P_35); also elsewhere on the board
/TopSheet/FPGA_1/FPGA_1_PMOD0_IO1: U10.A1 (IO_L1N_T0_AD4N_35); also elsewhere on the board
/TopSheet/FPGA_1/FPGA_1_PMOD0_IO2: U10.C2 (IO_L2P_T0_AD12P_35); also elsewhere on the board
/TopSheet/FPGA_1/FPGA_1_PMOD0_IO3: U10.B2 (IO_L2N_T0_AD12N_35); also elsewhere on the board
/TopSheet/FPGA_1/FPGA_1_PMOD0_IO4: U10.E1 (IO_L3P_T0_DQS_AD5P_35); also elsewhere on the board
/TopSheet/FPGA_1/FPGA_1_PMOD0_IO5: U10.D1 (IO_L3N_T0_DQS_AD5N_35); also elsewhere on the board
/TopSheet/FPGA_1/FPGA_1_PMOD0_IO6: U10.E2 (IO_L4P_T0_35); also elsewhere on the board
/TopSheet/FPGA_1/FPGA_1_PMOD0_IO7: U10.D2 (IO_L4N_T0_35); also elsewhere on the board
/TopSheet/FPGA_1/FPGA_1_PMOD1_IO0: U10.G1 (IO_L5P_T0_AD13P_35); also elsewhere on the board
/TopSheet/FPGA_1/FPGA_1_PMOD1_IO1: U10.F1 (IO_L5N_T0_AD13N_35); also elsewhere on the board
/TopSheet/FPGA_1/FPGA_1_PMOD1_IO2: U10.F3 (IO_L6P_T0_35); also elsewhere on the board
/TopSheet/FPGA_1/FPGA_1_PMOD1_IO3: U10.E3 (IO_L6N_T0_VREF_35); also elsewhere on the board
/TopSheet/FPGA_1/FPGA_1_PMOD1_IO4: U10.K1 (IO_L7P_T1_AD6P_35); also elsewhere on the board
/TopSheet/FPGA_1/FPGA_1_PMOD1_IO5: U10.J1 (IO_L7N_T1_AD6N_35); also elsewhere on the board
/TopSheet/FPGA_1/FPGA_1_PMOD1_IO6: U10.H2 (IO_L8P_T1_AD14P_35); also elsewhere on the board
/TopSheet/FPGA_1/FPGA_1_PMOD1_IO7: U10.G2 (IO_L8N_T1_AD14N_35); also elsewhere on the board
/TopSheet/FPGA_1/FPGA_1_PMOD2_IO0: U10.K2 (IO_L9P_T1_DQS_AD7P_35); also elsewhere on the board
/TopSheet/FPGA_1/FPGA_1_PMOD2_IO1: U10.J2 (IO_L9N_T1_DQS_AD7N_35); also elsewhere on the board
/TopSheet/FPGA_1/FPGA_1_PMOD2_IO2: U10.J5 (IO_L10P_T1_AD15P_35); also elsewhere on the board
/TopSheet/FPGA_1/FPGA_1_PMOD2_IO3: U10.H5 (IO_L10N_T1_AD15N_35); also elsewhere on the board
/TopSheet/FPGA_1/FPGA_1_PMOD2_IO4: U10.H3 (IO_L11P_T1_SRCC_35); also elsewhere on the board
/TopSheet/FPGA_1/FPGA_1_PMOD2_IO5: U10.G3 (IO_L11N_T1_SRCC_35); also elsewhere on the board
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
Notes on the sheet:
3.3V 1.8V 1.2V 1V
Program Reset (clears config)
135Mhz Displayport CLK
1.25V
Flash Memory selected from UG908
PROG DONE
SPI FLASH _> 100 (M0,M1,M2) JTAG _> 101 (M0,M1,M2) M0_2 default HIGH, Turning on SW pulls LOW SEE UG470 FOR MORE INFO
Pullups on USB_UART_JTAG Sheet
VCCINT _ 1V VCCAUX _ 1.8V VCCBRAM _ 1V VCCO _ 3.3V VCCBATT _ 1.8V VCCMGTAVCC _ 1V VCCMGTAVTT _ 1.2V VCCMGTREFCLK _ 1.2V VCCADC _ 1.8V VREFP _ 1.25V
FPGA_INITB will Go Low once initialization is done
FPGA USER IO
PROGRAM & DEVICE RESET
Required Artix_7 Voltage rails
FPGA CONFIG MEMORY
CONFIG STATUS
Device Reset (Does not clear config)
INIT_B Already Has Pullup, no need for FET Gate Pullup
FPGA_DONE will go High once Programming is done
200Mhz System CLK
FPGA ADC VREF
FPGA to FPGA 100-Bit Bus
INIT DONE
XADC ANALOG INPUT
Required Pull_up's
FPGA MODE SELECT
